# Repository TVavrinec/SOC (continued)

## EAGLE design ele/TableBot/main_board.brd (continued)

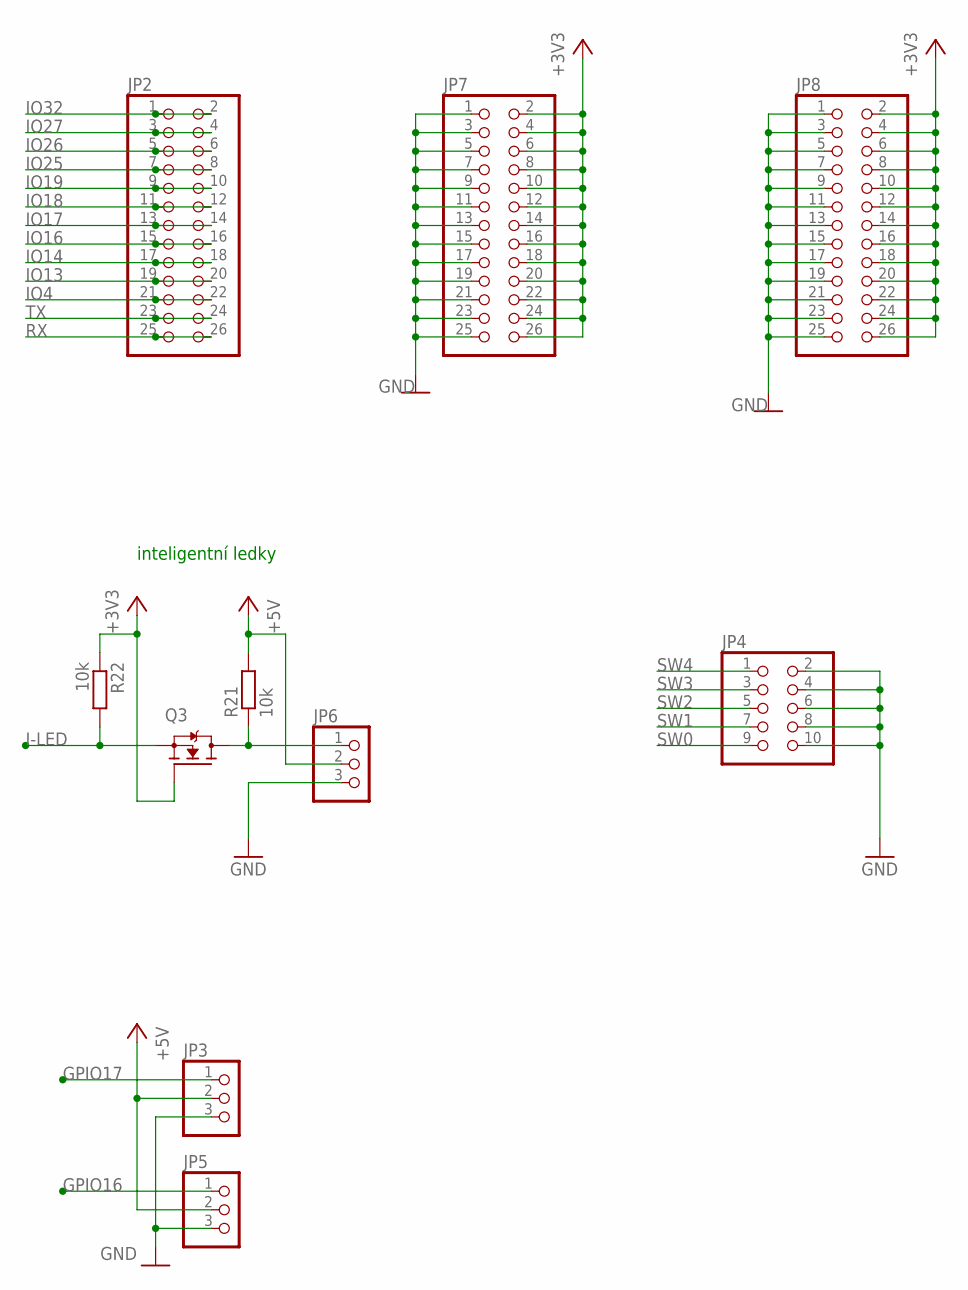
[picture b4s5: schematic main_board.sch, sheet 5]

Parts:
JP2, JP7, JP8: PINHD-2X13; 2X13
JP3, JP5, JP6: PINHD-1X3; 1X03
JP4: PINHD-2X5; 2X05
Q3: N-MOSFET-SOT23-DIST; SOT23_DIST
R21, R22: 10k; R0402

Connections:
+3V3: JP7.2, JP7.4, JP7.6, JP7.8, JP7.10, JP7.12, JP7.14, JP7.16, JP7.18, JP7.20, JP7.22, JP7.24, JP7.26, JP8.2, JP8.4, JP8.6, JP8.8, JP8.10, JP8.12, JP8.14, JP8.16, JP8.18, JP8.20, JP8.22, JP8.24, JP8.26, Q3.1 (G), R22.1; also elsewhere on the board
+5V: JP3.2, JP5.2, JP6.2, R21.2; also elsewhere on the board
GND: JP3.3, JP4.2, JP4.4, JP4.6, JP4.8, JP4.10, JP5.3, JP6.3, JP7.1, JP7.3, JP7.5, JP7.7, JP7.9, JP7.11, JP7.13, JP7.15, JP7.17, JP7.19, JP7.21, JP7.23, JP7.25, JP8.1, JP8.3, JP8.5, JP8.7, JP8.9, JP8.11, JP8.13, JP8.15, JP8.17, JP8.19, JP8.21, JP8.23, JP8.25; also elsewhere on the board
GPIO16: JP5.1
GPIO17: JP3.1
I-LED: Q3.2 (S), R22.2; also elsewhere on the board
IO4: JP2.21, JP2.22; also elsewhere on the board
IO13: JP2.19, JP2.20; also elsewhere on the board
IO14: JP2.17, JP2.18; also elsewhere on the board
IO16: JP2.15, JP2.16; also elsewhere on the board
IO17: JP2.13, JP2.14; also elsewhere on the board
IO18: JP2.11, JP2.12; also elsewhere on the board
IO19: JP2.9, JP2.10; also elsewhere on the board
IO25: JP2.7, JP2.8; also elsewhere on the board
IO26: JP2.5, JP2.6; also elsewhere on the board
IO27: JP2.3, JP2.4; also elsewhere on the board
IO32: JP2.1, JP2.2; also elsewhere on the board
unnamed: JP6.1, Q3.3 (D), R21.1
RX: JP2.25, JP2.26; also elsewhere on the board
SW0: JP4.9; also elsewhere on the board
SW1: JP4.7; also elsewhere on the board
SW2: JP4.5; also elsewhere on the board
SW3: JP4.3; also elsewhere on the board
SW4: JP4.1; also elsewhere on the board
TX: JP2.23, JP2.24; also elsewhere on the board

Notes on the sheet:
inteligentní ledky

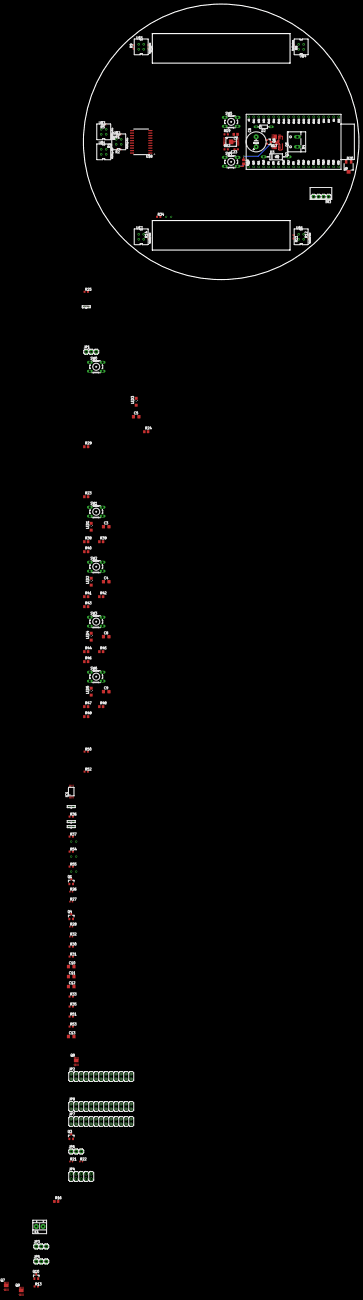
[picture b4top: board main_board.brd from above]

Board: 2 copper layers, 140.0 x 140.0 mm, 120 parts (1 on the bottom side), 90 nets.

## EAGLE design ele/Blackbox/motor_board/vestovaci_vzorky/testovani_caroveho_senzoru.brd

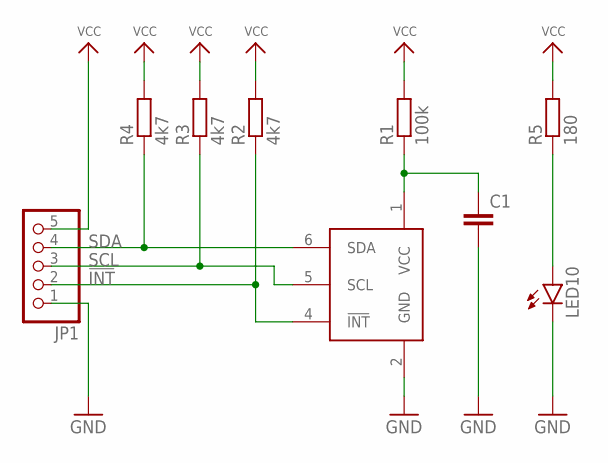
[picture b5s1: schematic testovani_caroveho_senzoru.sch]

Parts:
C1: C-EUC0603; C0603
ISL10: ISL29035
JP1: PINHD-1X5; 1X05
LED10: LEDCHIP-LED0603; CHIP-LED0603
R1: 100k; R0402
R2, R3, R4: 4k7; R0402
R5: 180; R0402

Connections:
!INT: ISL10.4 (!INT), JP1.2, R2.1
GND: C1.2, ISL10.2 (GND), JP1.1, LED10.C
unnamed: C1.1, ISL10.1 (VCC), R1.1
unnamed: LED10.A, R5.1
SCL: ISL10.5 (SCL), JP1.3, R3.1
SDA: ISL10.6 (SDA), JP1.4, R4.1
VCC: JP1.5, R1.2, R2.2, R3.2, R4.2, R5.2

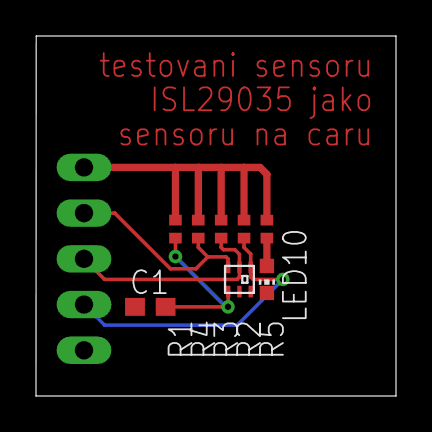
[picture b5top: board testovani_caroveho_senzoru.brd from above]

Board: 2 copper layers, 20.0 x 20.0 mm, 9 parts (1 on the bottom side), 7 nets.

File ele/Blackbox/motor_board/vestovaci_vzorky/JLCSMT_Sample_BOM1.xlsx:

Comment | Designator | Footprint | LCSC Part #（optional）
1uF | C1 | 0603_C | C15849
4.7KΩ | R2, R3, R4 | 0402_R | C25900
100KΩ | R1 | 0402_C | C25741
49.9Ω | R5 | 0402_R | C25120
 | ISL10 | ODFN-6_1.5x1.6x0.5P | C118347
 | LED10 | LED_0603 | C205443

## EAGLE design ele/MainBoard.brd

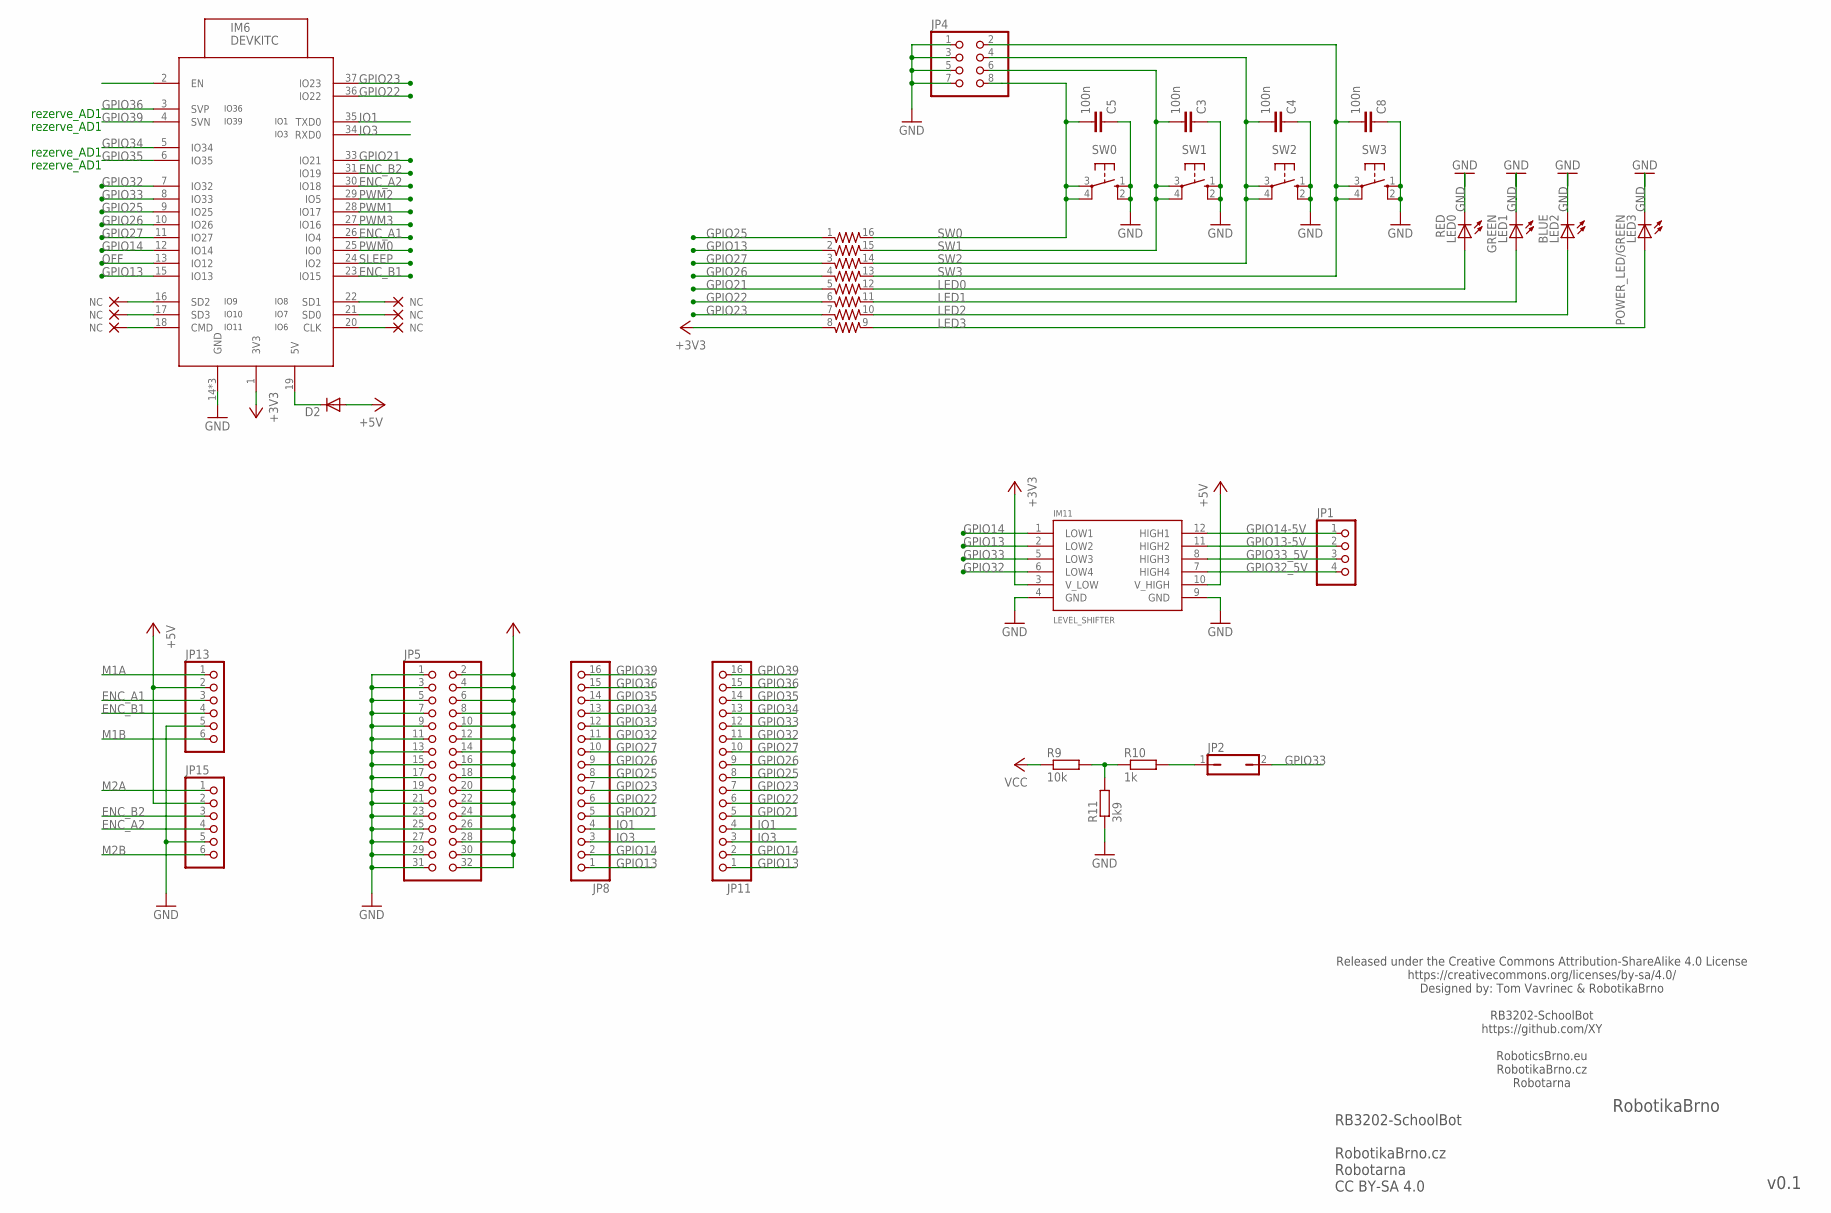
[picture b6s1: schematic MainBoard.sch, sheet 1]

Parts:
C3, C4, C5, C8: 100n; C1206
D2: DIODE-D-7.5; D-7.5
IM6: DEVKITC
IM11: LEVEL_SHIFTER
JP1: PINHD-1X4; 1X04
JP2: JP1Q; JP1
JP4: PINHD-2X4; 2X04
JP5: PINHD-2X16; 2X16
JP8, JP11: PINHD-1X16; 1X16
JP13, JP15: PINHD-1X6; 1X06
LED0: RED; LED3MM
LED1: GREEN; LED3MM
LED2: BLUE; LED3MM
LED3: POWER_LED/GREEN; LED3MM
R9: 10k; M0805
R10: 1k; M0805
R11: 3k9; M0805
RN1: 741-16_SNS; 742-16NS
SW0, SW1, SW2, SW3: 10-XX; B3F-10XX

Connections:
+3V3: IM6.1 (3V3), IM11.3 (V_LOW), JP5.2, JP5.4, JP5.6, JP5.8, JP5.10, JP5.12, JP5.14, JP5.16, JP5.18, JP5.20, JP5.22, JP5.24, JP5.26, JP5.28, JP5.30, JP5.32, RN1.8 (1); also elsewhere on the board
+5V: D2.A, IM11.10 (V_HIGH), JP13.2, JP15.2; also elsewhere on the board
+5V_ESP: D2.C, IM6.19 (5V)
ENC_A1: IM6.26 (IO4), JP13.3
ENC_A2: IM6.30 (IO18), JP15.4
ENC_B1: IM6.23 (IO15), JP13.4
ENC_B2: IM6.31 (IO19), JP15.3
GND: C3.1, C4.1, C5.1, C8.1, IM6.14 (GND), IM6.32 (GND), IM6.38 (GND), IM11.4 (GND), IM11.9 (GND), JP4.1, JP4.3, JP4.5, JP4.7, JP5.1, JP5.3, JP5.5, JP5.7, JP5.9, JP5.11, JP5.13, JP5.15, JP5.17, JP5.19, JP5.21, JP5.23, JP5.25, JP5.27, JP5.29, JP5.31, JP13.5, JP15.5, LED0.K (C), LED1.K (C), LED2.K (C), LED3.K (C), R11.1, SW0.1 (S), SW0.2 (S1), SW1.1 (S), SW1.2 (S1), SW2.1 (S), SW2.2 (S1), SW3.1 (S), SW3.2 (S1); also elsewhere on the board
GPIO13: IM6.15 (IO13), IM11.2 (LOW2), JP8.1, JP11.1, RN1.2 (1)
GPIO13-5V: IM11.11 (HIGH2), JP1.2
GPIO14: IM6.12 (IO14), IM11.1 (LOW1), JP8.2, JP11.2
GPIO14-5V: IM11.12 (HIGH1), JP1.1; also elsewhere on the board
GPIO21: IM6.33 (IO21), JP8.5, JP11.5, RN1.5 (1)
GPIO22: IM6.36 (IO22), JP8.6, JP11.6, RN1.6 (1)
GPIO23: IM6.37 (IO23), JP8.7, JP11.7, RN1.7 (1); also elsewhere on the board
GPIO25: IM6.9 (IO25), JP8.8, JP11.8, RN1.1
GPIO26: IM6.10 (IO26), JP8.9, JP11.9, RN1.4 (1)
GPIO27: IM6.11 (IO27), JP8.10, JP11.10, RN1.3 (1)
GPIO32: IM6.7 (IO32), IM11.6 (LOW4), JP8.11, JP11.11
GPIO32_5V: IM11.7 (HIGH4), JP1.4
GPIO33: IM6.8 (IO33), IM11.5 (LOW3), JP2.2, JP8.12, JP11.12
GPIO33_5V: IM11.8 (HIGH3), JP1.3
GPIO34: IM6.5 (IO34), JP8.13, JP11.13
GPIO35: IM6.6 (IO35), JP8.14, JP11.14
GPIO36: IM6.3 (SVP), JP8.15, JP11.15
GPIO39: IM6.4 (SVN), JP8.16, JP11.16
IO1: IM6.35 (TXD0), JP8.4, JP11.4
IO3: IM6.34 (RXD0), JP8.3, JP11.3
IO9_NC: IM6.16 (SD2)
IO9_NC1: IM6.20 (CLK)
IO10_NC: IM6.17 (SD3)
IO10_NC1: IM6.21 (SD0)
IO11_NC: IM6.18 (CMD)
IO11_NC1: IM6.22 (SD1)
LED0: LED0.A, RN1.12 (2)
LED1: LED1.A, RN1.11 (2)
LED2: LED2.A, RN1.10 (2)
LED3: LED3.A, RN1.9 (2)
M1A: JP13.1; also elsewhere on the board
M1B: JP13.6; also elsewhere on the board
M2A: JP15.1; also elsewhere on the board
M2B: JP15.6; also elsewhere on the board
unnamed: JP2.1, R10.2
unnamed: R9.2, R10.1, R11.2
OFF: IM6.13 (IO12); also elsewhere on the board
PWM0: IM6.25 (IO0); also elsewhere on the board
PWM1: IM6.28 (IO17); also elsewhere on the board
PWM2: IM6.29 (IO5); also elsewhere on the board
PWM3: IM6.27 (IO16); also elsewhere on the board
SLEEP: IM6.24 (IO2); also elsewhere on the board
SW0: C5.2, JP4.8, RN1.16 (2), SW0.3, SW0.4 (P1)
SW1: C3.2, JP4.6, RN1.15 (2), SW1.3, SW1.4 (P1)
SW2: C4.2, JP4.4, RN1.14 (2), SW2.3, SW2.4 (P1)
SW3: C8.2, JP4.2, RN1.13 (2), SW3.3, SW3.4 (P1)
VCC: R9.1; also elsewhere on the board

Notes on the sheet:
rezerve_AD1
RB3202-SchoolBot RobotikaBrno.cz Robotarna CC BY-SA 4.0
RobotikaBrno
v0.1
Released under the Creative Commons Attribution-ShareAlike 4.0 License https://creativecommons.org/licenses/by-sa/4.0/ Designed by: Tom Vavrinec & RobotikaBrno RB3202-SchoolBot https://github.com/XY RoboticsBrno.eu RobotikaBrno.cz Robotarna

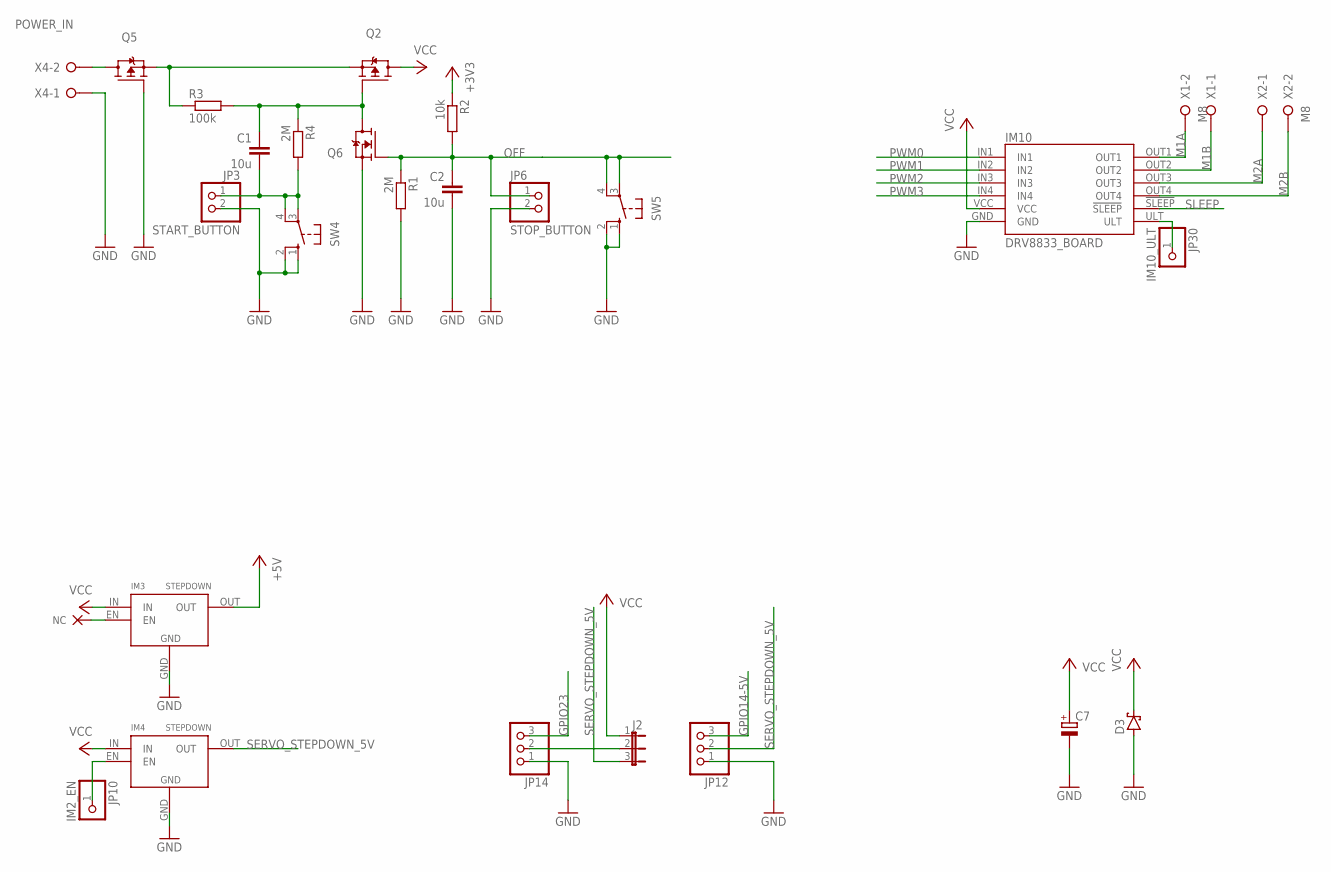
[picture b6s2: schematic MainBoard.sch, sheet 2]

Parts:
C1, C2: 10u; C1206
C7: CPOL-EUE5-10.5; E5-10,5
D3: SCHOTTKY-DIODEF126Z12; F126Z12
IM3, IM4: STEPDOWN
IM10: DRV8833_BOARD; PINHEAD
J2: JP2E; JP2
JP3: START_BUTTON; 1X02
JP6: STOP_BUTTON; 1X02
JP10: IM2_EN; 1X01
JP12, JP14: PINHD-1X3; 1X03
JP30: IM10_ULT; 1X01
Q2, Q5: P-MOSFET-TO220V; TO220V
Q6: N-MOSFET-SOT23-GSD; SOT23
R1: 2M; R0805
R2: 10k; 0204V
R3: 100k; R0805
R4: 2M; M0805
SW4, SW5: 10-XX; B3F-10XX
X1, X2: M8; W237-132
X4: POWER_IN; W237-132

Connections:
+3V3: R2.1; also elsewhere on the board
+5V: IM3.OUT; also elsewhere on the board
BAT1: Q5.2 (D), X4.2
BAT_PROT1: Q2.3 (S), Q5.3 (S), R3.1
GND: C2.2, C7.-, D3.A, IM3.GND, IM4.GND, IM10.GND, JP3.2, JP6.2, JP12.1, JP14.1, Q5.1 (G), Q6.2 (S), R1.2, SW4.1 (S), SW4.2 (S1), SW5.1 (S), SW5.2 (S1), X4.1; also elsewhere on the board
GPIO14-5V: JP12.3; also elsewhere on the board
GPIO23: JP14.3; also elsewhere on the board
IO9_NC2: IM3.EN
M1A: IM10.OUT1, X1.2; also elsewhere on the board
M1B: IM10.OUT2, X1.1; also elsewhere on the board
M2A: IM10.OUT3, X2.1; also elsewhere on the board
M2B: IM10.OUT4, X2.2; also elsewhere on the board
unnamed: IM10.ULT, JP30.1
unnamed: J2.2, JP14.2
OFF: C2.1, JP6.1, Q6.1 (G), R1.1, R2.2, SW5.3, SW5.4 (P1); also elsewhere on the board
PWM0: IM10.IN1; also elsewhere on the board
PWM1: IM10.IN2; also elsewhere on the board
PWM2: IM10.IN3; also elsewhere on the board
PWM3: IM10.IN4; also elsewhere on the board
SERVO_STEPDOWN_5V: IM4.OUT, J2.3, JP12.2
SLEEP: IM10.!SLEEP; also elsewhere on the board
START_BUTTON1: C1.2, JP3.1, R4.2, SW4.3, SW4.4 (P1)
START_GATE1: C1.1, Q2.1 (G), Q6.3 (D), R3.2, R4.1
STEP2_EN1: IM4.EN, JP10.1
VCC: C7.+, D3.C, IM3.IN, IM4.IN, IM10.VCC, J2.1, Q2.2 (D); also elsewhere on the board

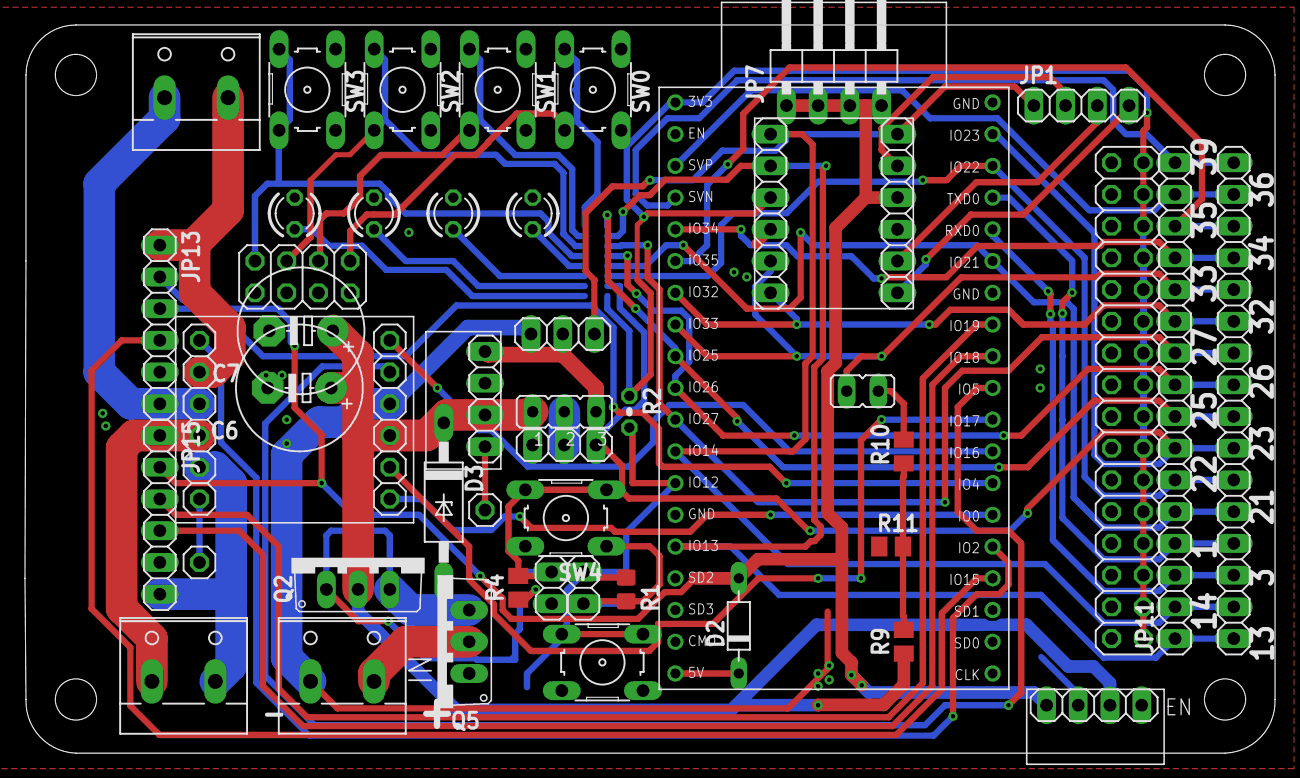
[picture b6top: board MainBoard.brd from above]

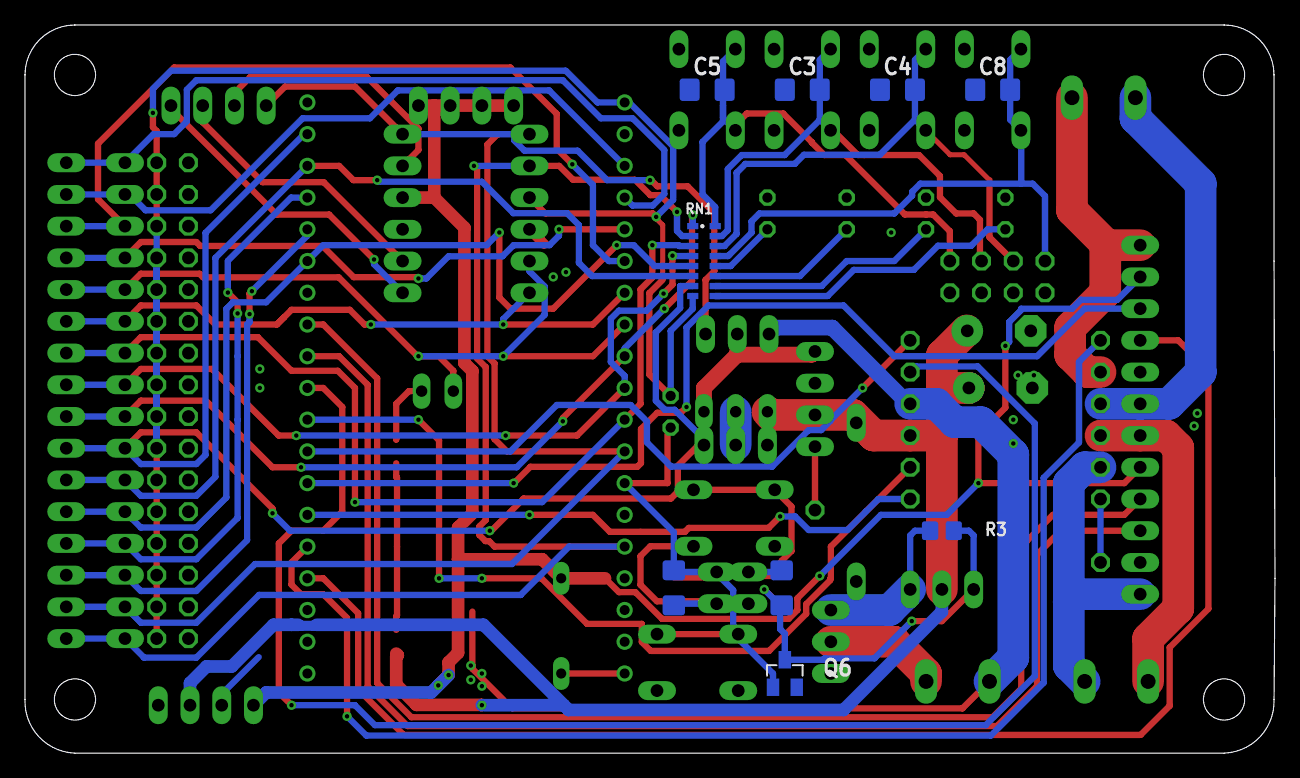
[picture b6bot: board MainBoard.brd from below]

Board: 2 copper layers, 100.1 x 58.3 mm, 55 parts (9 on the bottom side), 57 nets.

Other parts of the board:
C6: E5-10,5
JP7: 1X04/90

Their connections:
+5V: JP7.1, JP7.2, JP7.3, JP7.4; also elsewhere on the board
GND: C6.-; also elsewhere on the board
VCC: C6.+; also elsewhere on the board

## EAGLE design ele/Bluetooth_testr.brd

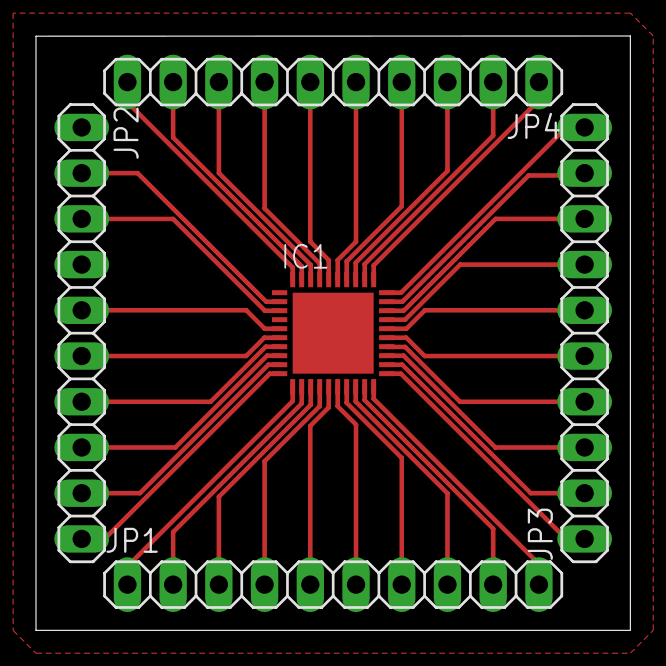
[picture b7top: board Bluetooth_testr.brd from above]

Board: 2 copper layers, 33.0 x 33.0 mm, 5 parts (0 on the bottom side), 39 nets.

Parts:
IC1: CC2541; QFN40-6X6
JP1, JP2, JP3, JP4: 1X10

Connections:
GND: IC1.1, JP2.1
unnamed: IC1.2, JP2.2
unnamed: IC1.3, JP2.3
unnamed: IC1.5, JP2.5
unnamed: IC1.6, JP2.6
unnamed: IC1.7, JP2.7
unnamed: IC1.8, JP2.8
unnamed: IC1.9, JP2.9
unnamed: IC1.10, JP2.10
unnamed: IC1.11, JP1.1
unnamed: IC1.12, JP1.2
unnamed: IC1.13, JP1.3
unnamed: IC1.14, JP1.4
unnamed: IC1.15, JP1.5
unnamed: IC1.16, JP1.6
unnamed: IC1.17, JP1.7
unnamed: IC1.18, JP1.8
unnamed: IC1.19, JP1.9
unnamed: IC1.26, JP3.6
unnamed: IC1.21, JP3.1
unnamed: IC1.22, JP3.2
unnamed: IC1.23, JP3.3
unnamed: IC1.24, JP3.4
unnamed: IC1.25, JP3.5
unnamed: IC1.20, JP1.10
unnamed: IC1.27, JP3.7
unnamed: IC1.28, JP3.8
unnamed: IC1.29, JP3.9
unnamed: IC1.30, JP3.10
unnamed: IC1.31, JP4.1
unnamed: IC1.32, JP4.2
unnamed: IC1.33, JP4.3
unnamed: IC1.34, JP4.4
unnamed: IC1.35, JP4.5
unnamed: IC1.36, JP4.6
unnamed: IC1.37, JP4.7
unnamed: IC1.38, JP4.8
unnamed: IC1.39, JP4.9
unnamed: IC1.40, JP4.10

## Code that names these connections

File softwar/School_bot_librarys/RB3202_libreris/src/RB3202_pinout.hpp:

#pragma once

#include <driver/adc.h>
#include <driver/gpio.h>

namespace RB3202
{  
    static const gpio_num_t BOARD_OFF = GPIO_NUM_13;

    static const gpio_num_t PWM_M0 = GPIO_NUM_0;
    static const gpio_num_t PWM_M1 = GPIO_NUM_16;
    static const gpio_num_t PWM_M2 = GPIO_NUM_17;
    static const gpio_num_t PWM_M3 = GPIO_NUM_5;
    static const gpio_num_t SLEEP_PIN = GPIO_NUM_2;

    static const gpio_num_t ENC_A1 = GPIO_NUM_15;
    static const gpio_num_t ENC_B1 = GPIO_NUM_4;
    static const gpio_num_t ENC_A2 = GPIO_NUM_19;
    static const gpio_num_t ENC_B2 = GPIO_NUM_18;


    static const gpio_num_t SW0 = GPIO_NUM_25;
    static const gpio_num_t SW1 = GPIO_NUM_12;
    static const gpio_num_t SW2 = GPIO_NUM_27;
    static const gpio_num_t SW3 = GPIO_NUM_26;

    static const gpio_num_t LED_r = GPIO_NUM_21;
    static const gpio_num_t LED_g = GPIO_NUM_22;
    static const gpio_num_t LED_b = GPIO_NUM_23;

    static const gpio_num_t SMART_SERVO = GPIO_NUM_23;

    static const gpio_num_t BATERI = GPIO_NUM_35;
};

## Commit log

2019-06-23 Revert "1"
    This reverts commit 7179373f5f77261e8855657630418cdeddee1971.
2019-06-23 prvni_commit_z_masiny
2019-06-23 bluethooth_testr
2019-06-23 battery_meter
2019-06-23 better
2019-06-23 popisky
2019-06-23 clean
2019-06-23 gitignore
2019-06-23 pinout
2019-06-23 RDC/screw hole
2019-06-23 ele: MainBoard - Add CC BY-SA license, fix pinheads position
2019-06-23 Improve .gitignore for Eagle
2019-06-24 condenser
2019-06-24 ladeni
2019-06-24 fix_errors
    oprava chyb routovani
2019-06-24 Rename PCB MainBoard to SchoolBot, release v0.1, add cam for Gatema
2019-06-26 libraries
    prvni cast knihoven
2019-06-26 nove funkce a pinout
    -doplneni pinoutu
    -dokonceni zakladnich funkci pro motor
2019-06-26 doplneni funkce stop
    -doplneni funkce stop
    -presun motor_start_working do pablic
2019-07-04 off pin
    presun vypinani desky na pin 13 kvuli nahrav8ni programu
2019-07-09 program ovladani serv
    zatim jen s lehce upravenym RBControl
2019-07-14 new board
    -komplenti prekreslini desky
    -doplneni rady pinhedu gnd pro 5v piniste
2019-07-15 nove rozlozeni
2019-07-15 new_board
    nesting noveho rozlozeni
2019-07-18 nove rozlozeni
    konecne zaroutovano
2019-07-18 FirstTableBot
    schema desky
2019-07-22 improvizovavi_PID
    -PID funguje jen neji napsany v knihovne
    ale je jen tak v mainu
2019-07-22 PID-ladeni_konstant
2019-07-23 PID
    přepsani PIDu do knihovny
2019-07-26 funsce go_position
2019-07-27 par oprav
2019-07-27 oprava gramatiki
2019-07-27 oprava
2019-07-27 test
2019-07-28 Vzber sensoru
2019-07-28 program_libreries
    navrat ke starší verzy
2019-07-29 oprava mereni
2019-07-29 schem
2019-07-30 Schoolbot
    -PID je v knihovne a je plne funkcni
2019-07-30 PID
    momentalne je funkcni otazka jak to bude priste mozna zas prestane fungovat vazne nevim.
2019-07-31 drobnosti
2019-07-31 RB3202_jednotny_konektor_na_motory
2019-07-31 zmena ATtiny
2019-08-05 DRV8833_jen_svab
2019-08-07 mereni proudu
2019-08-28 ir led pro encodery
2019-08-28 poznamkty k soucastkam
2019-09-08 upravi elektra
2019-09-08 schematická obměna OZ
2019-09-08 serialiyovani ir-led encoderu a zpetivoltovac I2C
2019-09-08 dolni propust k zesilovacum
2019-09-08 napajeni IR-led senzoru
2019-09-08 piniste
2019-09-16 zesilovace
2019-09-17 seznam soucastek na Schoolbota
2019-09-18 doplnění nakupu soucastek
2019-09-22 napájení z powerbanki
2019-09-28 nastrel_textu
2019-09-29 konkurence
2019-10-15 blackbox
2019-10-21 blackbox
    -led kruh
    -mpu6050
    -RTC
2019-10-23 blackbox-sch
2019-10-26 max485
    -max485
    -nejake datashity pouzitych soucastek
2019-10-30 eagle_librarys
2019-11-03 prvni_konzultace_s_kubou
2019-11-06 postup_pajeni_a_nejake_datadhity
2019-11-09 2.KSK
2019-11-10 dovetek_2.KSK
2019-11-11 3.KSK
2019-11-11 GPS_datashit
    NEO6M
2019-11-11 ESP32_wroom
    CH340C
2019-11-12 cicteni_pred_prvnim_nasazenim
2019-11-12 ladeni_drah
2019-11-15 jina_poloha_MPU6050
2019-11-16 srazeni_ceny
    -vymena_tranzistoru
2019-11-16 diry_pro_srouby
2019-11-17 vyrobni_data
2019-11-18 kondikyí_k_encoderu
2019-12-16 dokumentace ke SchoolBoardu
2019-12-17 SD-karta_na_BlackBoxu
2019-12-21 dalsi_text_a_firstbot
2020-01-04 BlackBox verze 1.0.0
2020-01-05 Text
2020-02-14 trochu v tom delam bordel
    proste to neumim delat poredne tak tet delam tenhle bordel commit bych mel vse na gitu a budu se snazit to dal delat poradne
2020-02-23 Max485
2020-03-10 softwar
